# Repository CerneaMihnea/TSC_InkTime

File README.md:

# InkTime Watch
---

## Descriere generala

InkTime este un ceas inteligent bazat pe microcontroller-ul **nRF52840** , care utilizeaza un display E-Paper (cerneala electronica) pentru afisarea orei si a altor informatii. Proiectul include design complet de schematic, PCB pe 4 straturi si modelare 3D a ansamblului, realizate in Autodesk Fusion.

Principalele caracteristici:
- Microcontroller nRF52840 cu Bluetooth 5.0 si procesor ARM Cortex-M4
- Display E-Paper conectat prin SPI
- Accelerometru/IMU pentru detectia miscarii (step counter, wake-on-wrist)
- Baterie LiPo cu circuit de incarcare dedicat
- Regulator DC/DC pentru tensiune stabila de 3.3V
- Fuel Gauge pentru monitorizarea nivelului bateriei
- Driver haptic pentru feedback vibrotactil
- Protectie ESD pe linia USB-C
- Conectivitate USB-C pentru incarcare si programare
- 3 butoane fizice pentru interactiune

---

## Diagrama bloc

```
                         +-------------------+
                         |    Baterie LiPo   |
                         +--------+----------+
                                  |
                         +--------v----------+
                         |  LiPo Charger     |  <-- USB-C (5V / VBUS)
                         |  BQ25180YBGR      |
                         +--------+----------+
                                  | VBAT (3.7-4.2V)
                         +--------v----------+
                         |  Fuel Gauge        |  <-- I2C --> nRF52840
                         |  MAX17048G+T10     |
                         +--------+----------+
                                  |
                         +--------v----------+
                         |  DC/DC Regulator  |  <-- I2C --> nRF52840
                         |  RT6160AWSC       |
                         +--------+----------+
                                  | 3V3
          +-----------------------+-----------------------+
          |                       |                       |
+---------v---------+   +---------v---------+   +---------v---------+
|   nRF52840 (U1)   |   |  ESD Protection   |   |   Butoane (x3)    |
|   Microcontroller |   |  USBLC6-2SC6Y     |   |   EVP-AKE31A      |
+---------+---------+   +-------------------+   +-------------------+
          |
    +-----+------+------+------+
    |            |      |      |
+---v---+  +----v--+  +-v---+ +-v---------+
| SPI   |  |  I2C  |  | SWD | | GPIO/ANT  |
+---+---+  +---+---+  +-----+ +-----------+
    |          |
+---v---+   +--+--+--+--+
|E-Paper|   | IMU | Haptic|
|Display|   |BMA423|DRV2605|
+-------+   +-------+-----+
```

---

## Bill of Materials (BOM)

| Cantitate | Componenta | Descriere | Referinta | 
|:---------:|:----------:|:---------:|:---------:|
| 1 | nRF52840 | Microcontroller ARM Cortex-M4, BT 5.0 | U1 | 
| 1 | BQ25180YBGR | LiPo Charger IC, 8-DSBGA | IC1 | 
| 1 | DRV2605YZFR | Haptic Driver ERM/LRA, 9-BGA | IC2 |
| 1 | BMA423 | IMU Accelerometru triaxial 12-bit | IC3 |
| 1 | MAX17048G+T10 | Fuel Gauge 1-Cell ModelGauge | U3 | 
| 1 | RT6160AWSC | Buck-Boost DC/DC Regulator I2C, 15-WL-CSP | IC9 | 
| 1 | USBLC6-2SC6Y | ESD Protection TVS Diode, SOT-23-6 | D3 | 
| 1 | KH-TYPE-C-16P | Conector USB-C 16 pini | J4 |
| 1 | 503480-2400 | Conector FPC/FFC 0.5mm 24 circuite | J1 | 
| 1 | DMG2305UX-7 | P-Channel MOSFET 20V/4.2A SOT-23 | Q2 | 
| 1 | SI1308EDL-T1-GE3 | N-Channel MOSFET 30V/1.5A SC-70 | Q3 | 
| 3 | MBR0530 | Dioda Schottky 30V/500mA SOD-123 | D1, D2, D5 | 
| 3 | EVP-AKE31A | Buton tactil SMD ultra-subtire | SW_DN, SW_ENT, SW_UP | 
| 1 | 2450AT18B100E | Antena 2.45GHz SMD | ANT1 | 
| 1 | FTC252012SR47MBCA | Inductor SMD 0.47uH 2016 | L7 | 
| 1 | 744043680 | Inductor SMD 68uH WE-TPC | L5 |
| 1 | TC2030-IDC | Conector Tag-Connect 6 pini SWD | J2 |
| 1 | X1 (32MHz) | Crystal 32MHz 2016 SMD | X1 |
| 1 | X2 (32.768kHz) | Crystal 32.768kHz 3215 SMD | X2 | 
| ~50 | Condensatoare SMD | 0201/0402, diverse valori (1pF - 22uF) | Cx | 
| ~15 | Rezistoare SMD | 0201, diverse valori (2.2Ω - 10kΩ) | Rx |
| ~4 | Inductoare SMD | 0402, diverse valori (3.9nH - 15nH, 10uH) | Lx |
| 14 | Test Pad TP20R | Test pad-uri SMD 2mm | TP_* |
| 1 | Solder Jumper SJ | Jumper SMD | SJ1 |

---

## Descrierea functionalitatii hardware

## Funcționalitate hardware

### Interfețe de comunicație
- **I2C**: LiPo Charger, DC/DC, IMU, Fuel Gauge, Haptic Driver  
- **SPI**: E-Paper Display Connector  

### Componente și roluri

- **nRF52840**  
  Microcontroller-ul principal care coordonează întreaga funcționalitate a plăcii.

- **IMU (Accelerometru)**  
  Măsoară accelerația pe cele trei axe.

- **LiPo Charger**  
  Responsabil pentru încărcarea bateriei.

- **DC/DC**  
  Stabilizator de tensiune ce furnizează 3.3V stabili întregii plăci.

- **E-Paper Drive Circuit**  
  Controlează funcționarea display-ului E-Paper.

- **Fuel Gauge**  
  Monitorizează nivelul de încărcare al bateriei.

- **Haptic Driver**  
  Controlează vibrațiile actuatorului (shaker).

- **USB-C Connector**  
  Asigură interfața de conectare USB.

- **ESD Protection**  
  Protejează placa împotriva descărcărilor electrostatice.

---

## Pinii nRF52840

Tabelul de mai jos descrie alocarea pinilor microcontroller-ului:

| Pin nRF52840 | Semnal | Modul conectat | Interfata | Descriere |
|-------------|--------|---------------|-----------|-----------|
| VDD | 3V3 | Alimentare | - | Alimentare la 3.3V |
| VSS | GND | Masa | - | Referinta de masa |
| P0.02/AIN0 | SCK | E-Paper Display | SPI | Clock serial SPI |
| P0.03/AIN1 | MOSI | E-Paper Display | SPI | Date catre display (Master Out Slave In) |
| P0.05/AIN3 | CS | E-Paper Display | SPI | Chip Select display |
| P0.15 | EPD_RST | E-Paper Display | GPIO | Reset display |
| P0.16 | EPD_DC | E-Paper Display | GPIO | Data/Command select |
| P0.17 | EPD_BUSY | E-Paper Display | GPIO | Stare ocupata display |
| P0.06 | SCL | IMU, LiPo Charger, DC/DC, Fuel Gauge, Haptic | I2C | Clock linie I2C |
| P0.07 | SDA | IMU, LiPo Charger, DC/DC, Fuel Gauge, Haptic | I2C | Date linie I2C |
| P0.08 | IMU_INT2 | BMA423 | GPIO | Intrerupere 2 accelerometru |
| P1.08 | IMU_INT1 | BMA423 | GPIO | Intrerupere 1 accelerometru |
| P0.10/NFC2 | FUELGAUGE_ALT | MAX17048 | GPIO | Alarma nivel scazut baterie |
| P0.11 | CHARGER_PG | BQ25180 | GPIO | Semnal Power Good charger |
| P0.12 | HAPTIC_EN | DRV2605 | GPIO | Enable driver haptic |
| P0.13 | BTN_UP | SW_UP | GPIO | Buton sus |
| P0.14 | BTN_ENT | SW_ENT | GPIO | Buton enter/confirmare |
| P1.02 | BTN_DN | SW_DN | GPIO | Buton jos |
| D+ | USB_DP | USB-C / ESD | USB | Date USB diferentiale pozitive |
| D- | USB_DM | USB-C / ESD | USB | Date USB diferentiale negative |
| VBUS | 5V USB | LiPo Charger | - | Alimentare 5V din USB |
| SWDIO | SWDIO | TC2030-IDC (J2) | SWD | Date programare/debug |
| SWDCLK | SWDCLK | TC2030-IDC (J2) | SWD | Clock programare/debug |
| SWO | SWO | TC2030-IDC (J2) | SWD | Trace output |
| P0.18/RESET | RESET | TC2030-IDC (J2) | GPIO | Reset hardware microcontroller |
| ANT | RF | 2450AT18B100E | RF | Antena Bluetooth 2.4GHz |
| XC1, XC2 | XTAL_32M | X1 (32 MHz) | Clock | Sursa de ceas principala |
| XL1, XL2 | XTAL_32K | X2 (32.768 kHz) | Clock | Sursa de ceas RTC (low power) |
| DEC1-DEC5 | GND | - | - | Condensatoare decuplare regulatoare interne |

---

## Design PCB si modelare 3D

### Stackup PCB — 4 straturi

Placa a fost realizata pe **4 straturi** pentru a asigura integritate de semnal buna si o rutare curata:

| Strat | Rol |
|-------|-----|
| Top (L1) | Rutare semnal + componente SMD |
| L2 | Plan de masa (GND) |
| L3 | Plan de 3.3V (VCC) |
| Bottom (L4) | Rutare semnal secundar |

Avantajele acestui stackup:
- Planul de masa L2 ofera un return path scurt pentru toate semnalele de pe L1
- Planul de 3.3V L3 reduce impedanta de alimentare si EMI
- Via-urile de semnal au return path minim intre straturi adiacente

### Decizii de design notabile

**Antena si decupaj PCB**: Antena 2450AT18B100E este pozitionata in coltul inferior al placii. Sub jumatatea neconectata electric a antenei, s-a realizat un **decupaj al substratului** (cutout) pentru a imbunatati performanta de radiatie si a evita absorbtia de semnal RF de catre materialul FR4.

**Via-in-pad**: Pentru componentele BGA (BQ25180, RT6160, DRV2605, MAX17048) cu pitch mic, s-au folosit **via-in-pad** — via-uri plasate direct sub pad-urile componentelor. Aceasta tehnica permite rutarea semnalelor in spatiu limitat, dar necesita umplere cu rasina (plugged vias) pentru a asigura planitate la lipire.

**Test pad-uri**: Sunt prevazute 14 test pad-uri (TP20R) pentru toate semnalele importante: 3V3, VBAT, GND, SDA, SCL, SWDCLK, SWDIO, SWO, RESET, VREG. Acestea faciliteaza testarea si depanarea dupa asamblare.

**Conexiuni baterie si shaker**: Bateria LiPo si motorul haptic (shaker) sunt conectate la PCB prin fire sudate pe test pad-urile dedicate (TP_VBAT, TP_VBAT_GND, respectiv pad-urile haptic driver-ului).

### Modelare 3D

Modelarea 3D a ansamblului ceasului a fost realizata in **Autodesk Fusion** si include:

- **PCB 3D** cu toate componentele plasate si orientate corect
- **Baterie LiPo** — model la nivel mediu de detaliu, cu fire de legatura rosu (+) si negru (-)
- **Display E-Paper** — model cu cadru verde si suprafata activa neagra, cu conector FPC/FFC
- **Shaker (motor haptic)** — model cilindric cu fire rosu si albastru
- **Carcasa** — carcasa inferioara si cadru superior de retentie display, fabricate din material negru
- **Exploded View** — vedere explodata verticala a ansamblului complet
- **Animatie** exploded view (disponibila in folderul Mechanical)

---

## Imagini

### Schematic

### PCB 2D

### PCB 3D

### Baterie

### Display E-Paper

### Shaker (Motor Haptic)

### Exploded View

## Diagrama de sistem — SVG

Diagrama bloc interactiva este disponibila in fisierul `inktime_diagram.svg` din radacina proiectului.

---

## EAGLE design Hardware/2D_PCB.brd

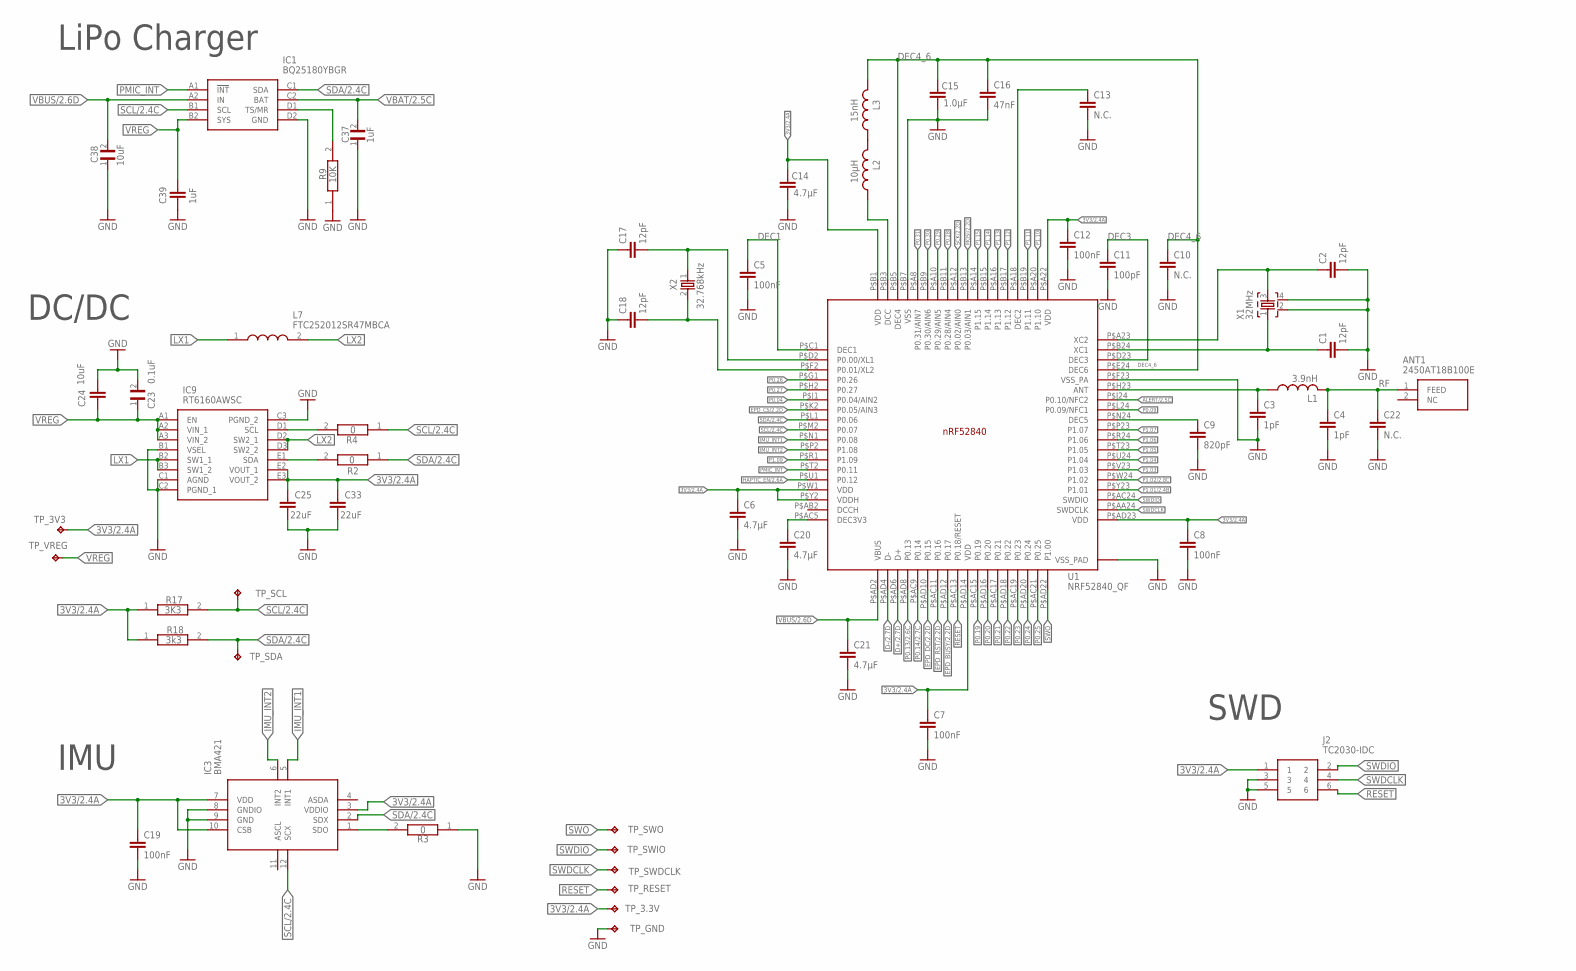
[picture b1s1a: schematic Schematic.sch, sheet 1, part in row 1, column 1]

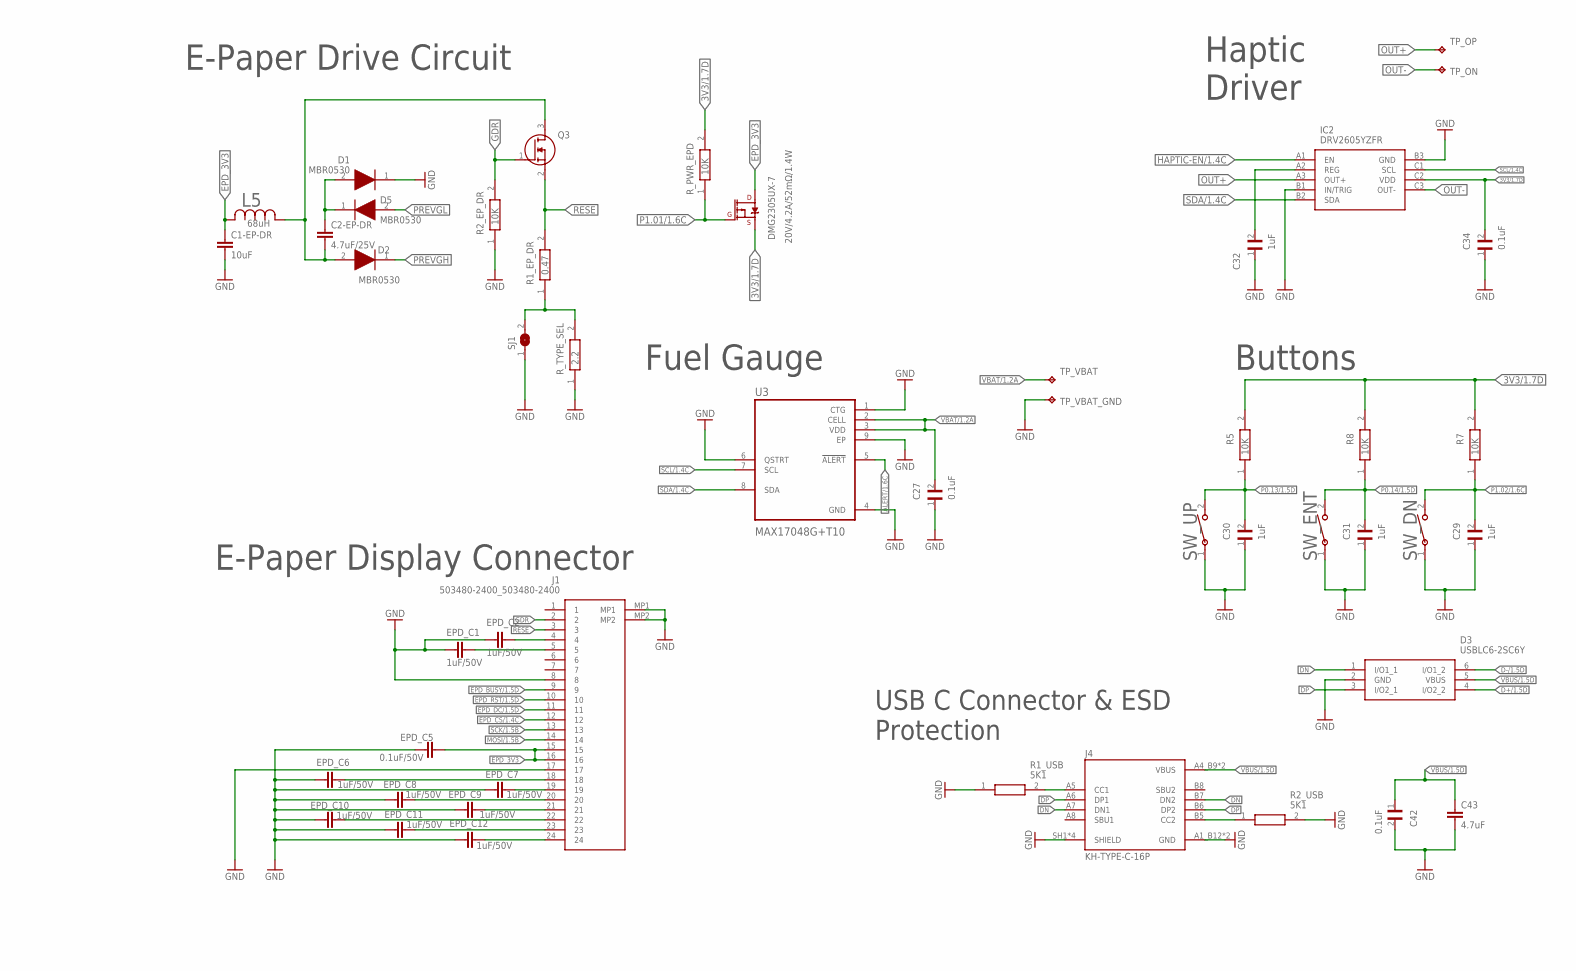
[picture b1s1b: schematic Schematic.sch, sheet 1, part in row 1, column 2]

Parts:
ANT1: 2450AT18B100E; 2450AT18B100E_ANTC3216X140N
C1, C2, C17, C18: 12pF; NORDIC_NRF_3_RESC0201_L
C1-EP-DR: 10uF; PERFECT_0402_0402
C2-EP-DR: 4.7uF/25V; PERFECT_0402_0402
C3, C4: 1pF; NORDIC_NRF_3_RESC0201_L
C5, C7, C8, C12, C19: 100nF; NORDIC_NRF_3_RESC0201_L
C6, C14, C20, C21: 4.7μF; NORDIC_NRF_3_RESC0402_L
C9: 820pF; NORDIC_NRF_3_RESC0201_L
C10, C13, C22: N.C.; NORDIC_NRF_3_RESC0201_L
C11: 100pF; NORDIC_NRF_3_RESC0201_L
C15: 1.0μF; NORDIC_NRF_3_RESC0402_L
C16: 47nF; NORDIC_NRF_3_RESC0201_L
C23, C27, C34, C42: 0.1uF; GRM011R60J152KE01L_2_CAPC0201X13N
C24: 10uF; NORDIC_NRF_3_RESC0402_L
C25, C33: 22uF; NORDIC_NRF_3_RESC0402_L
C29, C30, C31, C32, C37: 1uF; GRM011R60J152KE01L_2_CAPC0201X13N
C38: 10uF; GRM011R60J152KE01L_2_CAPC0201X13N
C39: 1uF; NORDIC_NRF_3_RESC0402_L
C43: 4.7uF; PERFECT_0402_0402
D1, D2, D5: MBR0530; ESP32_C6_LIBRARY_5_SOD3716X135N
D3: USBLC6-2SC6Y; ESP32_C6_LIBRARY_3_SOT95P280X145-6N
DMG2305UX-7: 20V/4.2A/52mΩ/1.4W; ESP32_C6_LIBRARY_4_ESP32_C6_LIBRARY_4_ESP32_C6_LIBRARY_4_ES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
EPD_C1, EPD_C2, EPD_C6, EPD_C7, EPD_C8, EPD_C9, EPD_C10, EPD_C11, EPD_C12: 1uF/50V; PERFECT_0402_0402
EPD_C5: 0.1uF/50V; NORDIC_NRF_3_RESC0201_L
IC1: BQ25180YBGR; BQ25180YBGR_BGA8C40P2X4_100X155X50
IC2: DRV2605YZFR; DRV2605YZFR_BGA9C50P3X3_144X144X62
IC3: BMA421; BMA423_BMA423
IC9: RT6160AWSC; RT6160AWSC_BGA15C40P3X5_140X230X60
J1: 503480-2400_503480-2400; 503480-2400_5034802400
J2: TC2030-IDC; TC2030-IDC_TC2030IDC
J4: KH-TYPE-C-16P; KH-TYPE-C-16P_KINGHELM_KH-TYPE-C-16P
L1: 3.9nH; NORDIC_NRF_2_RESC0402_L
L2: 10μH; NORDIC_NRF_2_RESC0402_L
L3: 15nH; NORDIC_NRF_2_RESC0402_L
L5: 68uH; ESP32_C6_LIBRARY_2_IND_4828-WE-TPC_WRE
L7: FTC252012SR47MBCA; MLP2016SR47MT0S1_INDC2016X100N
Q3: SI1308EDL-T1-GE3; ESP32_C6_LIBRARY_6_SOT65P210X110-3N
R1_EP_DR: 0.47; CPF0201D7K68C1_0201
R1_USB, R2_USB: 5K1; CPF0201D7K68C1_0201
R2, R3, R4: 0; CPF0201D7K68C1_0201
R2_EP_DR, R5, R7, R8, R9: 10K; CPF0201D7K68C1_0201
R17: 3K3; ERA-1AEB3401C_0201
R18: 3k3; ERA-1AEB3401C_0201
R_PWR_EPD: 10K; CPF0201D7K68C1_0201
R_TYPE_SEL: 2.2; CPF0201D7K68C1_0201
SJ1: ESP32_C6_LIBRARY_7_JUMPER_SJ
SW_DN: 2025-10-22_07-23-44_LIBRARY_EVP-AKE31ASW_EVP-AKE3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; 2025-10-22_07-23-44_LIBRARY_SW_EVP-AKE31A_PAN
SW_ENT: 2025-10-22_07-23-44_LIBRARY_EVP-AKE31ASW_EVP-AKE3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; 2025-10-22_07-23-44_LIBRARY_SW_EVP-AKE31A_PAN
SW_UP: 2025-10-22_07-23-44_LIBRARY_EVP-AKE31ASW_EVP-AKE3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; 2025-10-22_07-23-44_LIBRARY_SW_EVP-AKE31A_PAN
TP_3.3V, TP_3V3: HECTOR_WATCH_1_TPTP20R; HECTOR_WATCH_1_TP20R
TP_GND: HECTOR_WATCH_1_TPTP20R; HECTOR_WATCH_1_TP20R
TP_ON: HECTOR_WATCH_1_TPTP20R; HECTOR_WATCH_1_TP20R
TP_OP: HECTOR_WATCH_1_TPTP20R; HECTOR_WATCH_1_TP20R
TP_RESET: HECTOR_WATCH_1_TPTP20R; HECTOR_WATCH_1_TP20R
TP_SCL: HECTOR_WATCH_1_TPTP20R; HECTOR_WATCH_1_TP20R
TP_SDA: HECTOR_WATCH_1_TPTP20R; HECTOR_WATCH_1_TP20R
TP_SWDCLK: HECTOR_WATCH_1_TPTP20R; HECTOR_WATCH_1_TP20R
TP_SWIO: HECTOR_WATCH_1_TPTP20R; HECTOR_WATCH_1_TP20R
TP_SWO: HECTOR_WATCH_1_TPTP20R; HECTOR_WATCH_1_TP20R
TP_VBAT: HECTOR_WATCH_1_TPTP20R; HECTOR_WATCH_1_TP20R
TP_VBAT_GND: HECTOR_WATCH_1_TPTP20R; HECTOR_WATCH_1_TP20R
TP_VREG: HECTOR_WATCH_1_TPTP20R; HECTOR_WATCH_1_TP20R
U1: NRF52840_QF; NORDIC_NRF_4_AQFN50P700X700X85_HS-74N
U3: MAX17048G+T10; ESP32_C6_LIBRARY_SON50P200X200X80-9N
X1: 32MHz; NORDIC_NRF_BT-XTAL_2016_N
X2: 32.768kHz; NORDIC_NRF_1_XTAL_3215_N

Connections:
3V3/1.7D: C34.2, DMG2305UX-7.2 (S), IC2.C2 (VDD), R5.2, R7.2, R8.2, R_PWR_EPD.2
3V3/2.4A: C6.1, C7.1, C8.1, C12.1, C14.1, C19.1, C25.1, C33.1, IC3.3 (VDDIO), IC3.7 (VDD), IC3.10 (CSB), IC9.E2 (VOUT_1), IC9.E3 (VOUT_2), J2.1, R17.1, R18.1, TP_3.3V.TP, TP_3V3.TP, U1.P$A22 (VDD), U1.P$AD14 (VDD), U1.P$AD23 (VDD), U1.P$B1 (VDD), U1.P$W1 (VDD), U1.P$Y2 (VDDH)
ALERT/1.6C: U3.5 (!ALERT)
ALERT/2.5C: U1.P$J24 (P0.10/NFC2)
D+/1.5D: D3.4 (I/O2_2)
D+/2.7D: U1.P$AD6 (D+)
D-/1.5D: D3.6 (I/O1_2)
D-/2.7D: U1.P$AD4 (D-)
DEC1: C5.1, U1.P$C1 (DEC1)
DEC3: C11.1, U1.P$D23 (DEC3)
DEC4_6: C10.1, C15.1, C16.1, L3.2, U1.P$B5 (DEC4), U1.P$E24 (DEC6)
DN: D3.1 (I/O1_1), J4.A7 (DN1), J4.B7 (DN2)
DP: D3.3 (I/O2_1), J4.A6 (DP1), J4.B6 (DP2)
EPD_3V3: C1-EP-DR.1, DMG2305UX-7.3 (D), EPD_C5.2, J1.15, J1.16, L5.2
EPD_BUSY/1.5D: J1.9
EPD_BUSY/2.2D: U1.P$AD12 (P0.17)
EPD_CS/1.4C: J1.12
EPD_CS/2.2D: U1.P$K2 (P0.05/AIN3)
EPD_DC/1.5D: J1.11
EPD_DC/2.2D: U1.P$AD10 (P0.15)
EPD_RST/1.5D: J1.10
EPD_RST/2.2D: U1.P$AC11 (P0.16)
GDR: J1.2, Q3.1 (G), R2_EP_DR.2
GND: C1.2, C1-EP-DR.2, C2.2, C3.2, C4.2, C5.2, C6.2, C7.2, C8.2, C9.2, C10.2, C11.2, C12.2, C13.2, C14.2, C15.2, C16.2, C17.1, C18.1, C19.2, C20.2, C21.2, C22.2, C23.2, C24.1, C25.2, C27.1, C29.1, C30.1, C31.1, C32.1, C33.2, C34.1, C37.1, C38.1, C39.2, C42.2, C43.2, D1.1 (K), D3.2 (GND), EPD_C1.2, EPD_C2.2, EPD_C5.1, EPD_C6.2, EPD_C7.2, EPD_C8.2, EPD_C9.2, EPD_C10.2, EPD_C11.2, EPD_C12.2, IC1.D2 (GND), IC2.B1 (IN/TRIG), IC2.B3 (GND), IC3.8 (GNDIO), IC3.9 (GND), IC9.B1 (VSEL), IC9.C1 (AGND), IC9.C2 (PGND_1), IC9.C3 (PGND_2), J1.8, J1.17, J1.MP1, J1.MP2, J2.3, J2.5, J4.A1_B12 (GND), J4.A12_B1 (GND), J4.SH1 (SHIELD), J4.SH2 (SHIELD), J4.SH3 (SHIELD), J4.SH4 (SHIELD), R1_USB.1, R2_EP_DR.1, R2_USB.2, R3.1, R9.1, R_TYPE_SEL.1, SJ1.1, SW_DN.1, SW_ENT.1, SW_UP.1, TP_GND.TP, TP_VBAT_GND.TP, U1.P$74 (VSS_PAD), U1.P$75 (VSS_PAD), U1.P$76 (VSS_PAD), U1.P$77 (VSS_PAD), U1.P$78 (VSS_PAD), U1.P$79 (VSS_PAD), U1.P$80 (VSS_PAD), U1.P$81 (VSS_PAD), U1.P$82 (VSS_PAD), U1.P$83 (VSS_PAD), U1.P$84 (VSS_PAD), U1.P$85 (VSS_PAD), U1.P$86 (VSS_PAD), U1.P$87 (VSS_PAD), U1.P$88 (VSS_PAD), U1.P$89 (VSS_PAD), U1.P$90 (VSS_PAD), U1.P$B7 (VSS), U1.P$F23 (VSS_PA), U3.1 (CTG), U3.4 (GND), U3.6 (QSTRT), U3.9 (EP), X1.2, X1.4
HAPTIC-EN/1.4C: IC2.A1 (EN)
HAPTIC_EN/2.6A: U1.P$U1 (P0.12)
IMU_INT1: IC3.5 (INT1), U1.P$N1 (P0.08)
IMU_INT2: IC3.6 (INT2), U1.P$P2 (P1.08)
LX1: IC9.B2 (SW1_1), IC9.B3 (SW1_2), L7.1
LX2: IC9.D2 (SW2_1), IC9.D3 (SW2_2), L7.2
MOSI/1.5B: J1.14
MOSI/2.2D: U1.P$B13 (P0.03/AIN1)
unnamed: C3.1, L1.1, U1.P$H23 (ANT)
unnamed: IC9.D1 (SCL), R4.2
unnamed: C17.2, U1.P$D2 (P0.00/XL1), X2.1
unnamed: IC9.E1 (SDA), R2.2
unnamed: C18.2, U1.P$F2 (P0.01/XL2), X2.2
unnamed: L2.1, U1.P$B3 (DCC)
unnamed: IC1.D1 (TS/MR), R9.2
unnamed: L2.2, L3.1
unnamed: C2-EP-DR.1, D1.2 (A), D5.1 (K)
unnamed: C1.1, U1.P$B24 (XC1), X1.1
unnamed: IC3.1 (SDO), R3.2
unnamed: C2-EP-DR.2, D2.2 (A), L5.1, Q3.3 (D)
unnamed: C9.1, U1.P$N24 (DEC5)
unnamed: C2.1, U1.P$A23 (XC2), X1.3
unnamed: R1_EP_DR.1, R_TYPE_SEL.2, SJ1.2
unnamed: C32.2, IC2.A2 (REG)
unnamed: C20.1, U1.P$AC5 (DEC3V3)
unnamed: J4.B5 (CC2), R2_USB.1
unnamed: J4.A5 (CC1), R1_USB.2
unnamed: EPD_C2.1, J1.4
unnamed: EPD_C1.1, J1.5
unnamed: EPD_C6.1, J1.18
unnamed: EPD_C7.1, J1.19
unnamed: C13.1, U1.P$A18 (DEC2)
unnamed: EPD_C8.1, J1.20
unnamed: EPD_C9.1, J1.21
unnamed: EPD_C10.1, J1.22
unnamed: EPD_C11.1, J1.23
unnamed: EPD_C12.1, J1.24
OUT+: IC2.A3 (OUT+), TP_OP.TP
OUT-: IC2.C3 (OUT-), TP_ON.TP
P0.04: U1.P$J1 (P0.04/AIN2)
P0.09: U1.P$L24 (P0.09/NFC1)
P0.13/1.5D: C30.2, R5.1, SW_UP.2
P0.13/2.6C: U1.P$AD8 (P0.13)
P0.14/1.5D: C31.2, R8.1, SW_ENT.2
P0.14/2.7C: U1.P$AC9 (P0.14)
P0.19: U1.P$AC15 (P0.19)
P0.20: U1.P$AD16 (P0.20)
P0.21: U1.P$AC17 (P0.21)
P0.22: U1.P$AD18 (P0.22)
P0.23: U1.P$AC19 (P0.23)
P0.24: U1.P$AD20 (P0.24)
P0.25: U1.P$AC21 (P0.25)
P0.26: U1.P$G1 (P0.26)
P0.27: U1.P$H2 (P0.27)
P0.28: U1.P$B11 (P0.28/AIN4)
P0.29: U1.P$A10 (P0.29/AIN5)
P0.30: U1.P$B9 (P0.30/AIN6)
P0.31: U1.P$A8 (P0.31/AIN7)
P1.01/1.6C: DMG2305UX-7.1 (G), R_PWR_EPD.1
P1.01/2.4B: U1.P$Y23 (P1.01)
P1.02/1.6C: C29.2, R7.1, SW_DN.2
P1.02/2.8C: U1.P$W24 (P1.02)
P1.03: U1.P$V23 (P1.03)
P1.04: U1.P$U24 (P1.04)
P1.05: U1.P$T23 (P1.05)
P1.06: U1.P$R24 (P1.06)
P1.07: U1.P$P23 (P1.07)
P1.09: U1.P$R1 (P1.09)
P1.10: U1.P$A20 (P1.10)
P1.11: U1.P$B19 (P1.11)
P1.12: U1.P$B17 (P1.12)
P1.13: U1.P$A16 (P1.13)
P1.14: U1.P$B15 (P1.14)
P1.15: U1.P$A14 (P1.15)
PMIC_INT: IC1.A1 (!INT), U1.P$T2 (P0.11)
PREVGH: D2.1 (K)
PREVGL: D5.2 (A)
RESE: J1.3, Q3.2 (S), R1_EP_DR.2
RESET: J2.6, TP_RESET.TP, U1.P$AC13 (P0.18/RESET)
RF: ANT1.1 (FEED), C4.1, C22.1, L1.2
SCK/1.5B: J1.13
SCK/2.2D: U1.P$A12 (P0.02/AIN0)
SCL/1.4C: IC2.C1 (SCL), U3.7 (SCL)
SCL/2.4C: IC1.B1 (SCL), IC3.12 (SCX), R4.1, R17.2, TP_SCL.TP, U1.P$M2 (P0.07)
SDA/1.4C: IC2.B2 (SDA), U3.8 (SDA)
SDA/2.4C: IC1.C1 (SDA), IC3.2 (SDX), R2.1, R18.2, TP_SDA.TP, U1.P$L1 (P0.06)
SWDCLK: J2.4, TP_SWDCLK.TP, U1.P$AA24 (SWDCLK)
SWDIO: J2.2, TP_SWIO.TP, U1.P$AC24 (SWDIO)
SWO: TP_SWO.TP, U1.P$AD22 (P1.00)
VBAT/1.2A: C27.2, TP_VBAT.TP, U3.2 (CELL), U3.3 (VDD)
VBAT/2.5C: C37.2, IC1.C2 (BAT)
VBUS/1.5D: C42.1, C43.1, D3.5 (VBUS), J4.A4_B9 (VBUS), J4.A9_B4 (VBUS)
VBUS/2.6D: C21.1, C38.2, IC1.A2 (IN), U1.P$AD2 (VBUS)
VREG: C23.1, C24.2, C39.1, IC1.B2 (SYS), IC9.A1 (EN), IC9.A2 (VIN_1), IC9.A3 (VIN_2), TP_VREG.TP

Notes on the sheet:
LiPo Charger
DC/DC
IMU
SWD
E-Paper Drive Circuit
E-Paper Display Connector
Fuel Gauge
Haptic Driver
Buttons
USB C Connector & ESD Protection

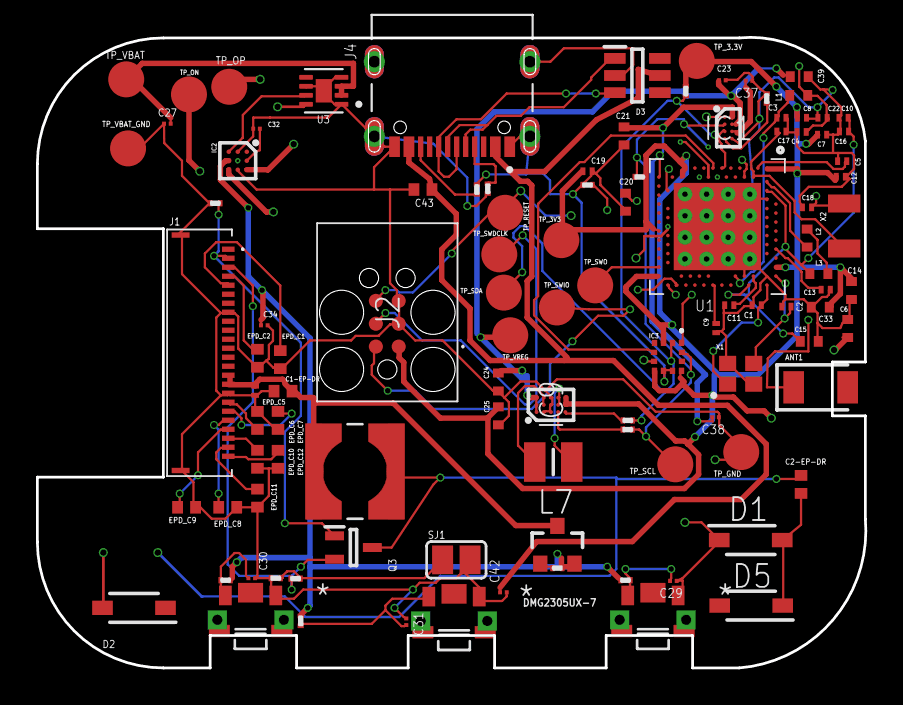
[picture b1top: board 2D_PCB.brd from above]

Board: 4 copper layers, 46.0 x 35.0 mm, 105 parts (0 on the bottom side), 65 nets.

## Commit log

2026-04-10 Added project first iteration
2026-04-17 Added Project Second Iteration
2026-04-17 Changed 2D PCB Photo
2026-04-17 Changed README
2026-04-17 Changed Schematic.pdf

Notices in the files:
parts and their libraries:
COPYRIGHT: Copyright (C) 2024 Ultra Librarian. All rights reserved.
COPYRIGHT: Copyright (C) 2025 Ultra Librarian. All rights reserved.
